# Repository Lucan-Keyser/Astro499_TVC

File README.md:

# Astro499_TVC

## GUI installation

1. Install the required processing vs code extensions. Search for processing in the extensions tab and install the following:
   - processing-language-server-extension by Diya Solanki
   - 
   - if errors when running close the window, close windows again on box selection, cancel the support solver
   - close the full terminal in vs code and hit green run button again

### Coordinate Standards jpg

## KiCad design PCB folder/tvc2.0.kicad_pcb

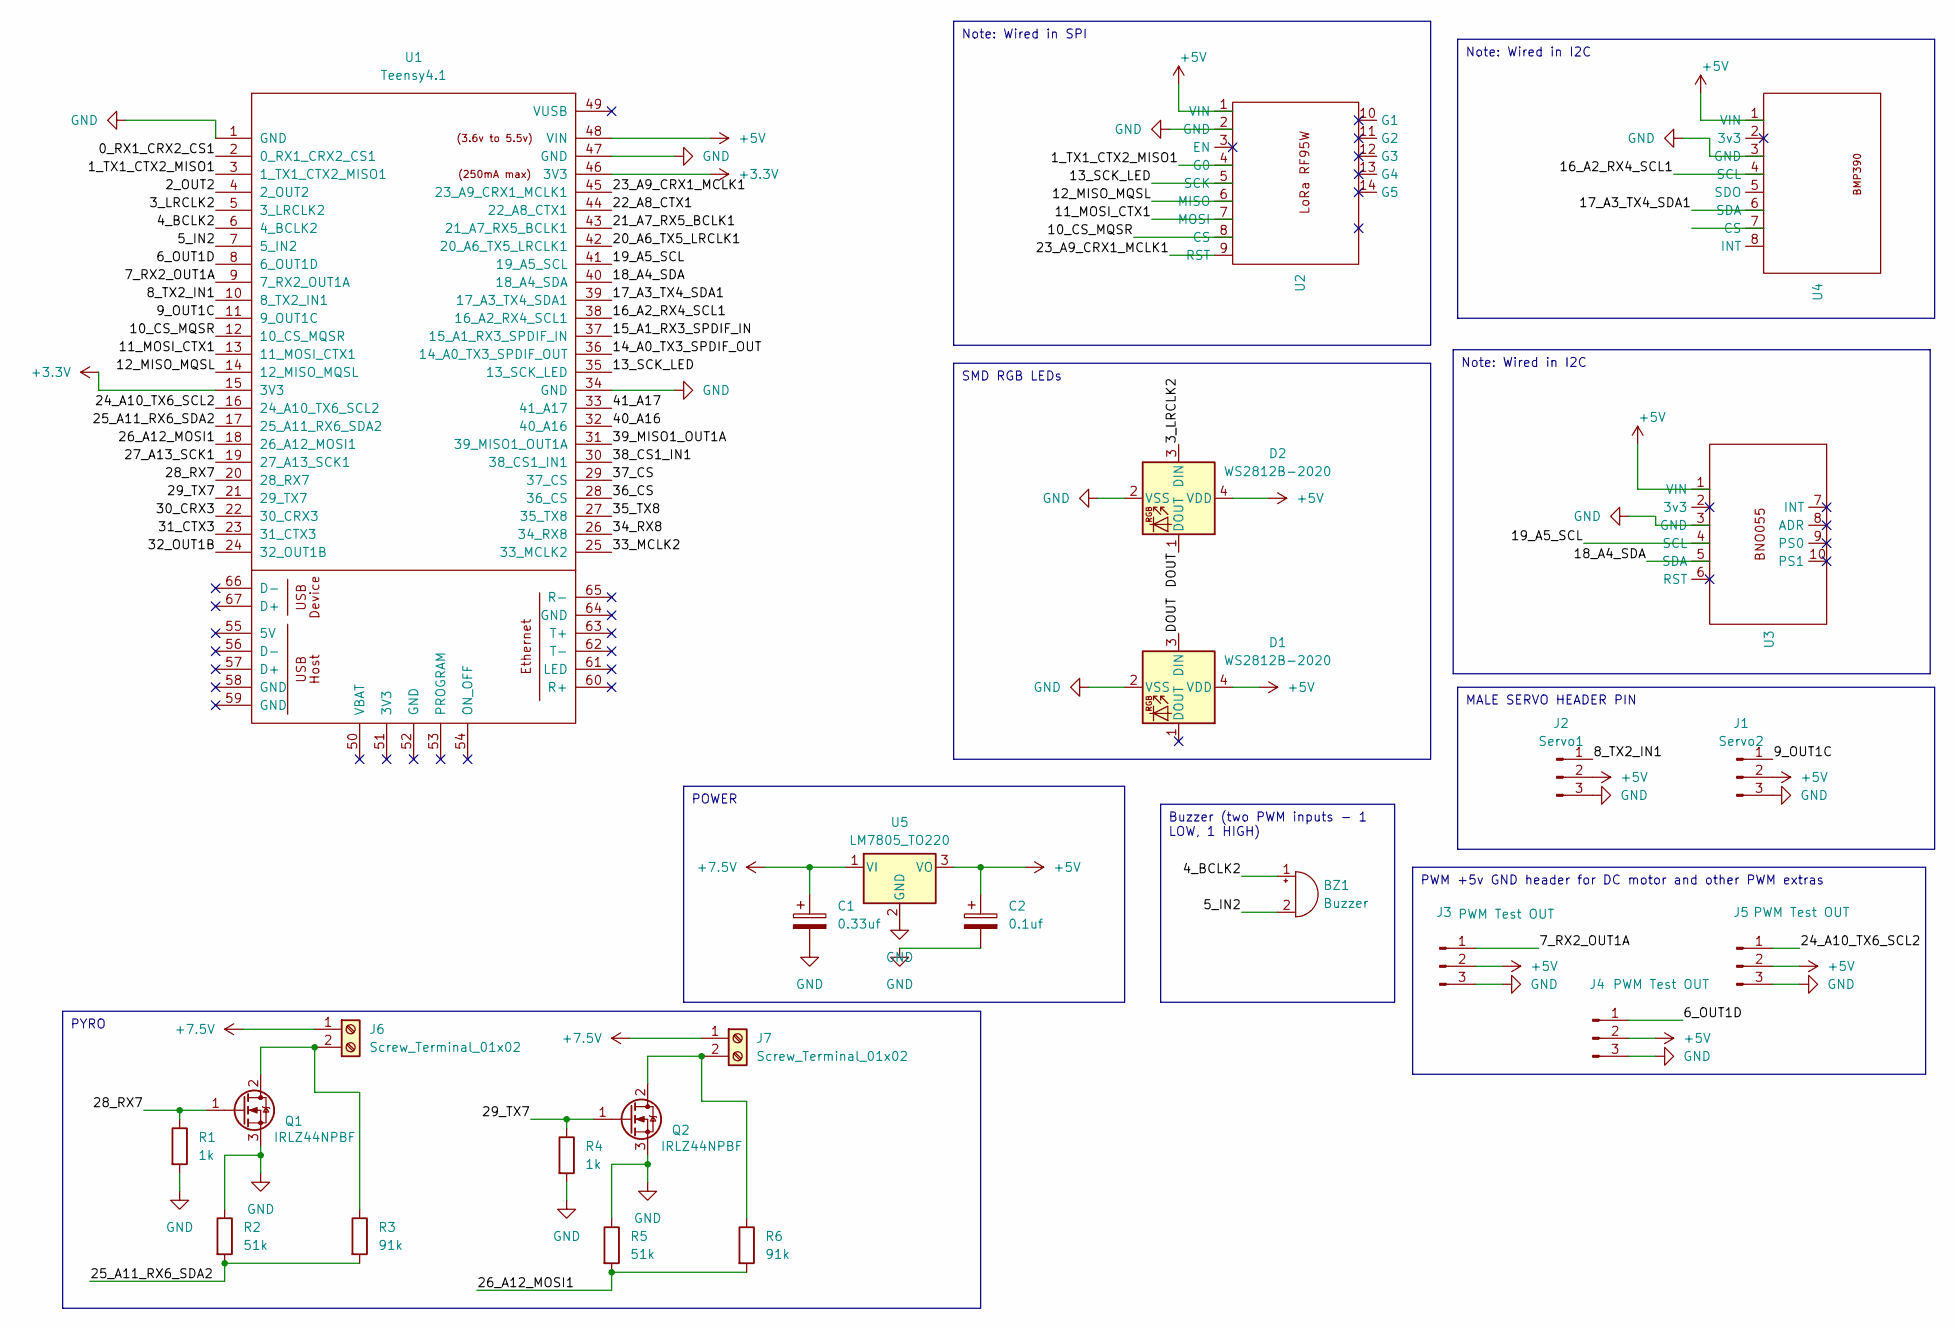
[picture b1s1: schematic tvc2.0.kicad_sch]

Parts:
BZ1: Buzzer; Buzzer_TDK_PS1240P02BT_D12.2mm_H6.5mm
C1: 0.33uf; C_1206_3216Metric
C2: 0.1uf; C_1206_3216Metric
D1, D2: WS2812B-2020; LED_WS2812B-2020_PLCC4_2.0x2.0mm
J1: Servo2; PinHeader_1x03_P2.54mm_Vertical
J2: Servo1; PinHeader_1x03_P2.54mm_Vertical
J3, J4, J5: PWM Test OUT; PinHeader_1x03_P2.54mm_Vertical
J6, J7: Screw_Terminal_01x02; TerminalBlock_Phoenix_MKDS-1,5-2-5.08_1x02_P5.08mm_Horizont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
Q1, Q2: IRLZ44NPBF; TO-220-3_Vertical
R1, R4: 1k; R_1206_3216Metric
R2, R5: 51k; R_1206_3216Metric
R3, R6: 91k; R_1206_3216Metric
U1: Teensy4.1; Teensy41
U2: LoRa_RF95 Breakout
U3: BNO055
U4: (no value)
U5: LM7805_TO220; SOT-223

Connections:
+3.3V: U1.15 (3V3), U1.46 (3V3)
+5V: C2.1, D1.4 (VDD), D2.4 (VDD), J1.2, J2.2, J3.2, J4.2, J5.2, U1.48 (VIN), U2.1 (VIN), U3.1 (VIN), U4.1 (VIN), U5.3 (VO)
+7.5V: C1.1, J6.1, J7.1, U5.1 (VI)
/0_RX1_CRX2_CS1: U1.2 (0_RX1_CRX2_CS1)
/1_TX1_CTX2_MISO1: U1.3 (1_TX1_CTX2_MISO1), U2.4 (G0)
/2_OUT2: U1.4 (2_OUT2)
/3_LRCLK2: D2.3 (DIN), U1.5 (3_LRCLK2)
/4_BCLK2: BZ1.1 (+), U1.6 (4_BCLK2)
/5_IN2: BZ1.2 (-), U1.7 (5_IN2)
/6_OUT1D: J4.1, U1.8 (6_OUT1D)
/7_RX2_OUT1A: J3.1, U1.9 (7_RX2_OUT1A)
/8_TX2_IN1: J2.1, U1.10 (8_TX2_IN1)
/9_OUT1C: J1.1, U1.11 (9_OUT1C)
/10_CS_MQSR: U1.12 (10_CS_MQSR), U2.8 (CS)
/11_MOSI_CTX1: U1.13 (11_MOSI_CTX1), U2.7 (MOSI)
/12_MISO_MQSL: U1.14 (12_MISO_MQSL), U2.6 (MISO)
/13_SCK_LED: U1.35 (13_SCK_LED), U2.5 (SCK)
/14_A0_TX3_SPDIF_OUT: U1.36 (14_A0_TX3_SPDIF_OUT)
/15_A1_RX3_SPDIF_IN: U1.37 (15_A1_RX3_SPDIF_IN)
/16_A2_RX4_SCL1: U1.38 (16_A2_RX4_SCL1), U4.4 (SCL)
/17_A3_TX4_SDA1: U1.39 (17_A3_TX4_SDA1), U4.6 (SDA)
/18_A4_SDA: U1.40 (18_A4_SDA), U3.5 (SDA)
/19_A5_SCL: U1.41 (19_A5_SCL), U3.4 (SCL)
/20_A6_TX5_LRCLK1: U1.42 (20_A6_TX5_LRCLK1)
/21_A7_RX5_BCLK1: U1.43 (21_A7_RX5_BCLK1)
/22_A8_CTX1: U1.44 (22_A8_CTX1)
/23_A9_CRX1_MCLK1: U1.45 (23_A9_CRX1_MCLK1)
/24_A10_TX6_SCL2: J5.1, U1.16 (24_A10_TX6_SCL2)
/25_A11_RX6_SDA2: R2.2, R3.2, U1.17 (25_A11_RX6_SDA2)
/26_A12_MOSI1: R5.2, R6.2, U1.18 (26_A12_MOSI1)
/27_A13_SCK1: U1.19 (27_A13_SCK1)
/28_RX7: Q1.1 (G), R1.1, U1.20 (28_RX7)
/29_TX7: Q2.1 (G), R4.1, U1.21 (29_TX7)
/30_CRX3: U1.22 (30_CRX3)
/31_CTX3: U1.23 (31_CTX3)
/32_OUT1B: U1.24 (32_OUT1B)
/33_MCLK2: U1.25 (33_MCLK2)
/34_RX8: U1.26 (34_RX8)
/35_TX8: U1.27 (35_TX8)
/36_CS: U1.28 (36_CS)
/37_CS: U1.29 (37_CS)
/38_CS1_IN1: U1.30 (38_CS1_IN1)
/39_MISO1_OUT1A: U1.31 (39_MISO1_OUT1A)
/40_A16: U1.32 (40_A16)
/41_A17: U1.33 (41_A17)
/DOUT: D1.3 (DIN), D2.1 (DOUT)
GND: C1.2, C2.2, D1.2 (VSS), D2.2 (VSS), J1.3, J2.3, J3.3, J4.3, J5.3, Q1.3 (S), Q2.3 (S), R1.2, R2.1, R4.2, R5.1, U1.1 (GND), U1.34 (GND), U1.47 (GND), U2.2 (GND), U3.3 (GND), U4.3 (GND), U5.2 (GND)
unnamed: J6.2, Q1.2 (D), R3.1
unnamed: J7.2, Q2.2 (D), R6.1

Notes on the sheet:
PWM +5v GND header for DC motor and other PWM extras
Note: Wired in I2C
Buzzer (two PWM inputs - 1 LOW, 1 HIGH)
MALE SERVO HEADER PIN
Note: Wired in I2C
PYRO
POWER
Note: Wired in SPI
SMD RGB LEDs

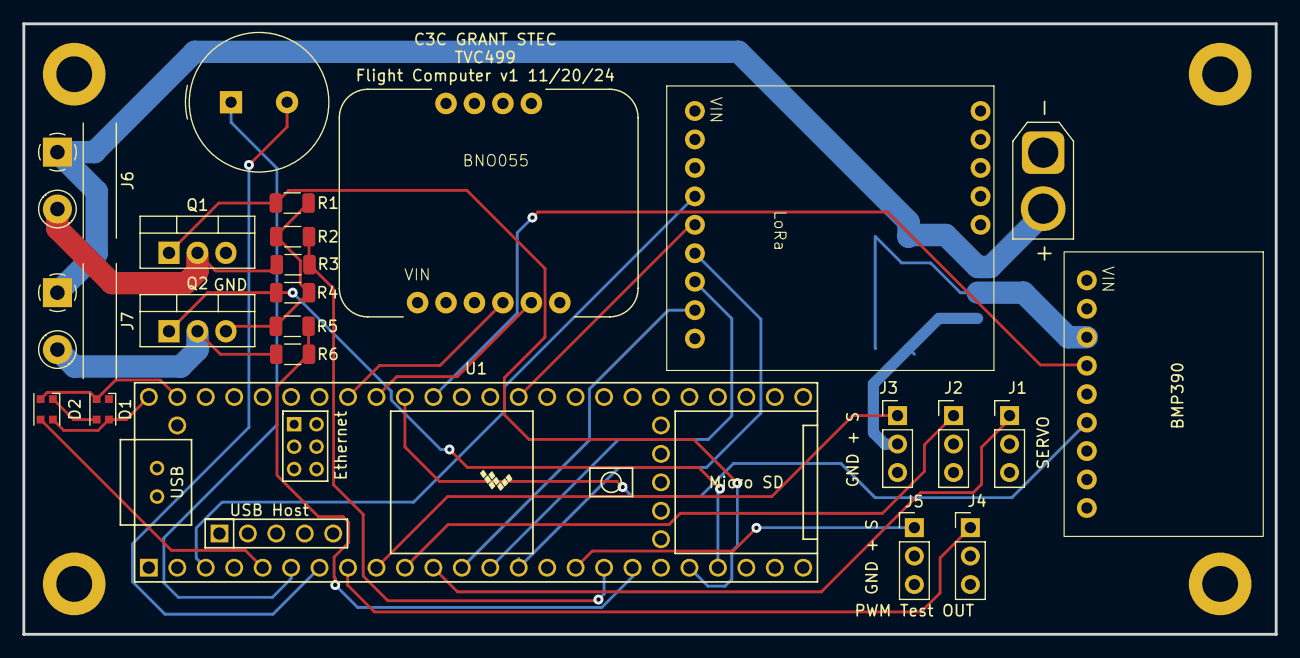
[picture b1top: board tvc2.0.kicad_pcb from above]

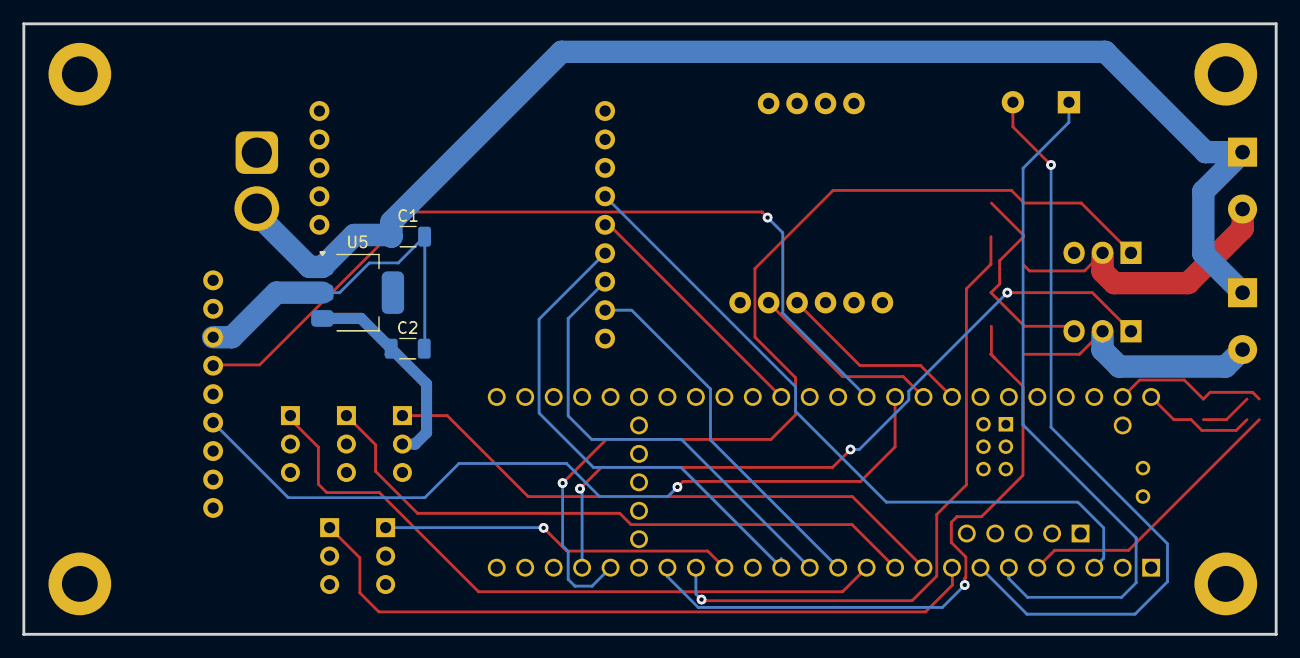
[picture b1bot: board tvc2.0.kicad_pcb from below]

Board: 4 copper layers, 111.8 x 54.5 mm, 25 parts (3 on the bottom side), 27 nets.

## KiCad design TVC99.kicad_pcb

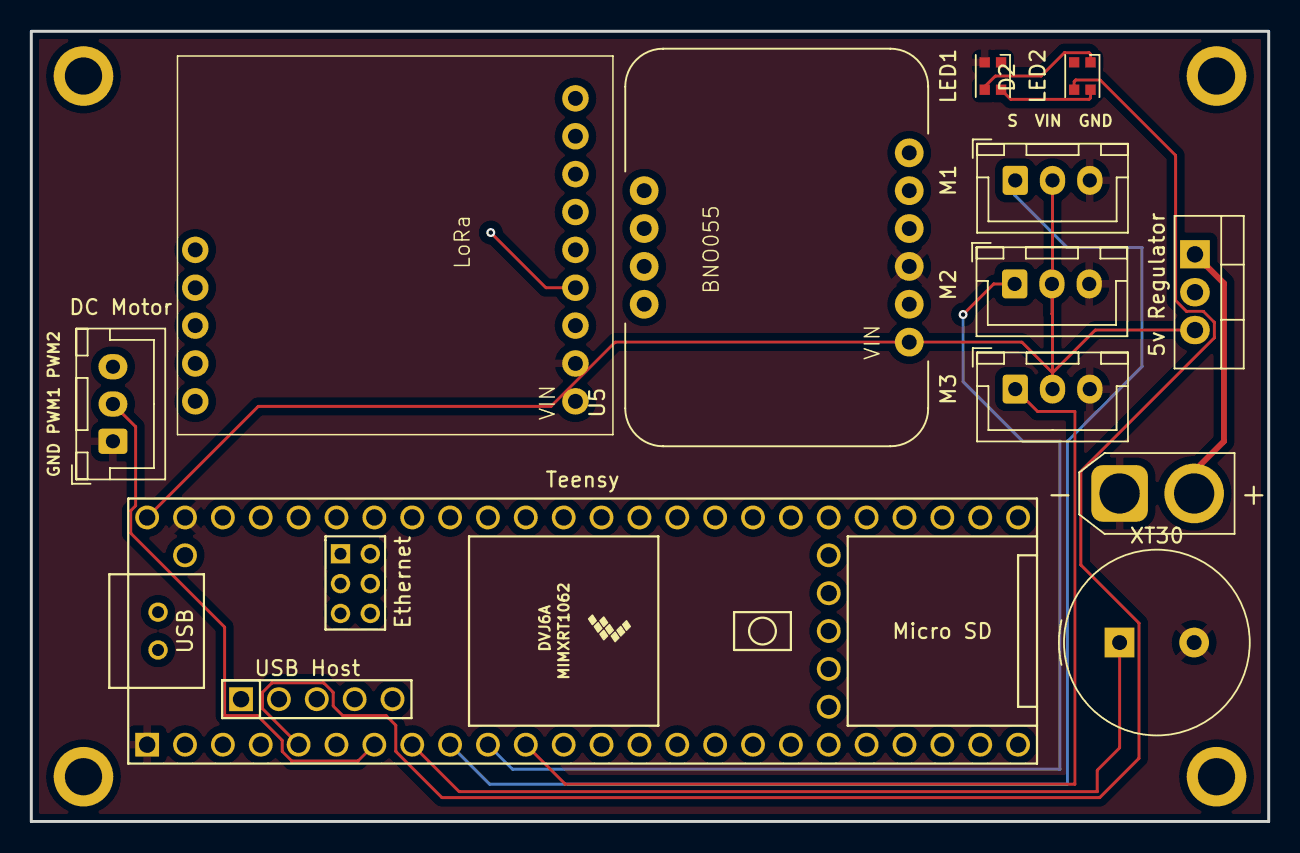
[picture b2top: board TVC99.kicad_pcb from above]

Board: 4 copper layers, 83.0 x 53.0 mm, 11 parts (0 on the bottom side), 15 nets.

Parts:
5v Regulator: LM7805_TO220; TO-220-3_Vertical
D1, D2: WS2812B-2020; LED_WS2812B-2020_PLCC4_2.0x2.0mm
DC Motor: PWM DC motor control; JST_XH_B3B-XH-A_1x03_P2.50mm_Vertical
M1, M2, M3: Motor_Servo; JST_XH_B3B-XH-A_1x03_P2.50mm_Vertical
Teensy: Teensy4.1; Teensy41
U3: LoRa_RF95 Breakout
U5: BNO055
XT30: Buzzer; Buzzer_TDK_PS1240P02BT_D12.2mm_H6.5mm

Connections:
+7.5V: D1.4 (VDD), D2.4 (VDD)
GND: 5v Regulator.2 (GND), D1.2 (VSS), D2.2 (VSS), DC Motor.1, M1.3 (-), M2.3 (-), M3.3 (-), Teensy.1 (GND), Teensy.47 (GND), U3.2 (G2), U5.3 (PS0), XT30.2 (-)
unnamed: Teensy.8 (6_OUT1D), XT30.1 (+)
unnamed: D1.3 (DIN), Teensy.5 (3_LRCLK2)
unnamed: D1.1 (DOUT), D2.3 (DIN)
unnamed: Teensy.3 (1_TX1_CTX2_MISO1), U3.4 (G4)
unnamed: M1.1 (PWM), Teensy.9 (7_RX2_OUT1A)
unnamed: M2.1 (PWM), Teensy.10 (8_TX2_IN1)
unnamed: M3.1 (PWM), Teensy.11 (9_OUT1C)
unnamed: Teensy.12 (10_CS_MQSR), U3.8 (GND)
unnamed: Teensy.13 (11_MOSI_CTX1), U3.7 (VIN)
unnamed: Teensy.14 (12_MISO_MQSL), U3.6 (Ant)
unnamed: Teensy.35 (13_SCK_LED), U3.5 (G5)
unnamed: Teensy.45 (23_A9_CRX1_MCLK1), U3.9 (EN)
unnamed: 5v Regulator.3 (VO), M1.2 (+), M2.2 (+), M3.2 (+), Teensy.48 (VIN), U3.1 (G1), U5.1 (INT)

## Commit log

2024-10-19 Commit Test
2024-10-24 ready to send to other team members
2024-10-24 Update README.md
    chore: updating README for expected commit message layout and integration of new code
2024-10-24 Create PCB folder
2024-10-24 docs: add pcb schematic file
    PCB schematic in KiCad. 1 Teensy, 3 servos, 2 BNO055, 1 BMP390, 1 RF95W, 1 W25Q12 flash mem, 2 IRLB8721PBF, 1 LM7805_TO220
2024-10-24 Create placeholder.txt and PCB folder
2024-10-24 docs: ki cad pcb schematic
    PCB schematic in KiCad. 1 Teensy, 3 servos, 2 BNO055, 1 BMP390, 1 RF95W, 1 W25Q12 flash mem, 2 IRLB8721PBF, 1 LM7805_TO220
2024-10-26 functs: added leds and buzzer to schematic
2024-10-29 docs: pcb files
2024-11-08 fix: new pcb design
    4 layers, inner two ground plane and +5v. Refined schematic.
2024-11-17 [Missing standardized message] Lt Col Harris MATLAB uploaded init
2024-11-18 funts: Added Pyro circuit in schematic
2024-11-20 functs: update PCB, add part excel
2024-11-20 New order sheet
2024-11-20 added pcb name date version
2024-11-21 Simulink modelV1.slx first version
2024-11-25 edit: final pcb files sent to JLC
2024-11-25 functs: final parts order
2024-12-05 reciever code
2024-12-05 edits for lora transmitter
2024-12-06 GUI GSE
2024-12-06 Modified: made the 3DOF block use external gravity so we aren't just canceling it out and creating constant velocity.
2024-12-08 physically tested PID loop
2024-12-18 experimentation.
2024-12-20 GUI files
2024-12-26 Add files via upload
    Updated thrust force modeling
2024-12-26 Updated variable naming, added code for plot visualization
2024-12-26 Updated thrust force input
2024-12-27 Meeting w/ Lt Col Harris. Determined next steps and fixed scope issue.
2025-01-30 disconnect and connect w buttons
2025-01-31 Latest FC code
2025-02-17 updated receiver code
2025-02-17 updated gui code
2025-03-25 Began 6DOF Model and Reorganized Some Files
2025-03-27 Force of Thrust at angle 6DOF and F15-0 Model in 6DOF
2025-04-01 Added clock and sim cutoff
2025-04-02 Added moments probably wrong
2025-04-03 Debug 6DOF Moment and Coordinate Transform
2025-04-03 clean up
2025-04-03 added platform io and comp sci standard
2025-04-03 initial platform io setup
2025-04-04 hardware, sensors, comms
2025-04-04 additional changes for pyros, buzzer, lora, gyro offsets
2025-04-08 Added Coordinate Standards Image
2025-04-09 Updated to Plant to fix Thrust and Moment.
    Gravity Still broken
2025-04-10 6DOF With Torque Feedback Control
    Still need to fix initial angle. I suspect there is a coordinate frame issue. But it works as of now. No actuators, straight torque feedback with LQR control. Roll torque is zeroed.
2025-04-10 6DOF 2024a
    Roll torque has been removed like in flight.
2025-04-12 imu update
2025-04-12 Combination of Gravity and LQR
2025-04-12 Gravity and LQR Commit 2
    fixed autosave thing
2025-04-12 xml upload for Grant
2025-04-12 xml again | started to isolate movement
2025-04-13 More LQR debug attempts
    Leftovers from Friday Meeting
2025-04-14 Quaternion state estimation and control with servo outputs.
2025-04-15 Quaternion update with gravity, got accelerometer values, better controller/servo abstraction, updated config file
2025-04-16 Full tate machine, sensor updates, logging framework, config file updates
2025-04-17 Push for grant testing
2025-04-19 lora bugs
2025-04-19 debug
2025-04-19 push for grant
2025-04-19 for claude
2025-04-19 more claude
2025-04-19 push
2025-04-20 end of Friday changes
2025-04-20 good
2025-04-20 Add initial project structure and source files for Receiver Code
2025-04-20 cleanup for flight
2025-04-20 flight sum excel NO UPDATE
2025-04-21 Excel Ready for TRR with Test Objectives
2025-04-22 acell fixes
2025-04-24 SDIO sd card added
2025-04-24 Initial OOP
2025-04-24 cleanup imu class
2025-04-24 cleanup
2025-04-24 sesnor cleanup
2025-04-24 initialize func
2025-04-24 idea
2025-04-24 Sensors, control, hardware, and actuators classes complete
2025-04-24 Removed servos from control
2025-04-24 Communication almost done
2025-04-24 added servo test
2025-04-24 Grant watch this
2025-04-25 Push for claude
2025-04-25 lora testing
2025-04-25 Fixed SD issue
2025-04-27 Push for grant.
2025-04-27 Push before old code test
2025-04-28 Launch ready
2025-04-29 servo adds
2025-05-01 Start of Monte Carlo - run simulink from matlab
    - renamed a bunch of stuff
    - currently has both experimental and old versions of the simulink. need to delete the old one
    - aim is to create an experimental branch where communication is less important, but it can be merged with or deconflicted with the main branch once we have a stable & understood version of the code/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
2025-05-02 Beginnning Kalman Filter
